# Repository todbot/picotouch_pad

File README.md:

# picotouch_pad
picotouch MIDI controller, but pad-based

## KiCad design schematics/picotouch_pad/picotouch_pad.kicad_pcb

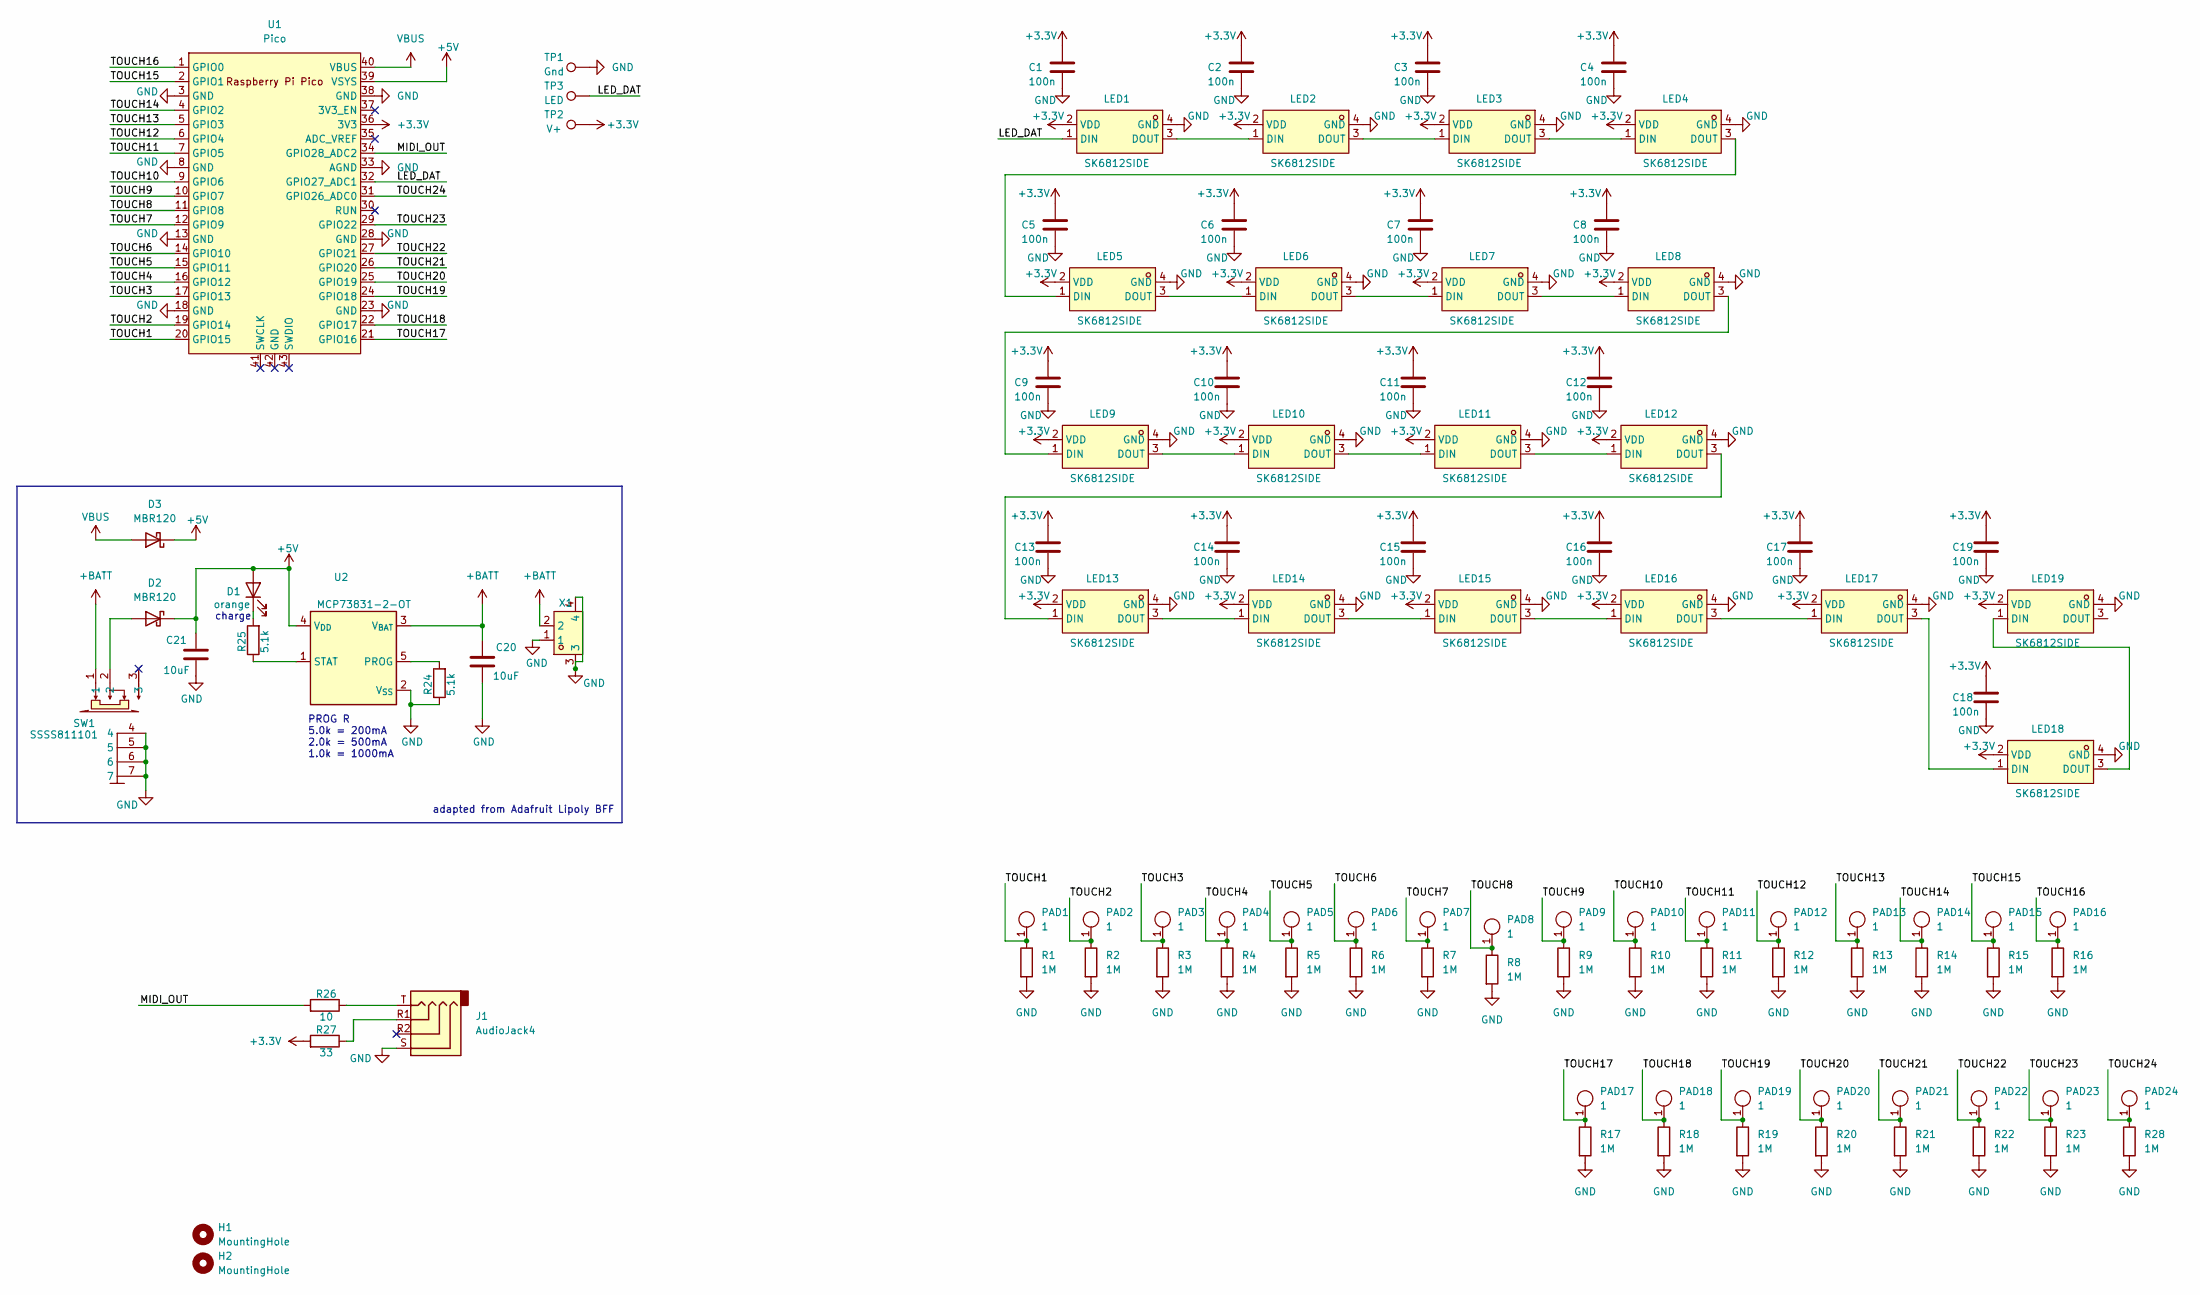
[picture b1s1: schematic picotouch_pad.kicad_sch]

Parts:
C1, C2, C3, C4, C5, C6, C7, C8, C9, C10, C11, C12, C13, C14, C15, C16, C17, C18, C19: 100n; C_0603_1608Metric
C20, C21: 10uF; C_0603_1608Metric
D1: orange; LED_0603_1608Metric
D2, D3: MBR120; D_SOD-123F; LCSC Part C130880
H1, H2: MountingHole; MountingHole_2.7mm_M2.5
J1: AudioJack4; Jack_3.5mm_PJ320D_Horizontal; LCSC C431535
LED1, LED2, LED3, LED4, LED5, LED6, LED7, LED8, LED9, LED10, LED11, LED12, LED13, LED14, LED15, LED16, LED17, LED18, LED19: SK6812SIDE; LED-SMD_4P-L4.0-W1.6-L-keepoutrev; LCSC Part C5378721
PAD1, PAD2, PAD3, PAD4, PAD5, PAD6, PAD7, PAD8, PAD9, PAD10, PAD11, PAD12, PAD13, PAD14, PAD15, PAD16: 1; Pad-CapTouch-10mm-roundrect
PAD17, PAD18, PAD19, PAD20, PAD21, PAD22, PAD23, PAD24: 1; Pad-CapTouch-10x5mm-roundrect
R1, R2, R3, R4, R5, R6, R7, R8, R9, R10, R11, R12, R13, R14, R15, R16, R17, R18, R19, R20, R21, R22, R23, R28: 1M; R_0603_1608Metric
R24, R25: 5.1k; R_0603_1608Metric
R26: 10; R_0603_1608Metric
R27: 33; R_0603_1608Metric
SW1: SSSS811101; SW-SMD_SSSS811101; LCSC Part C109335
TP1: Gnd; TestPoint_Pad_D1.5mm
TP2: V+; TestPoint_Pad_D1.5mm
TP3: LED; TestPoint_Pad_D1.5mm
U1: Pico; RPi_Pico_SMD
U2: MCP73831-2-OT; SOT-23-5; LCSC Part C424093
X1: AFC20-S02ACA-00; CONN-SMD_AFC20-S02ACA-00; LCSC Part C2764211

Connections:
+3.3V: C1.1, C2.1, C3.1, C4.1, C5.1, C6.1, C7.1, C8.1, C9.1, C10.1, C11.1, C12.1, C13.1, C14.1, C15.1, C16.1, C17.1, C18.1, C19.1, LED1.2 (VDD), LED2.2 (VDD), LED3.2 (VDD), LED4.2 (VDD), LED5.2 (VDD), LED6.2 (VDD), LED7.2 (VDD), LED8.2 (VDD), LED9.2 (VDD), LED10.2 (VDD), LED11.2 (VDD), LED12.2 (VDD), LED13.2 (VDD), LED14.2 (VDD), LED15.2 (VDD), LED16.2 (VDD), LED17.2 (VDD), LED18.2 (VDD), LED19.2 (VDD), R27.2, TP2.1, U1.36 (3V3)
+5V: C21.1, D1.2 (A), D2.1 (K), D3.1 (K), U1.39 (VSYS), U2.4 (V_{DD})
+BATT: C20.1, SW1.1, U2.3 (V_{BAT}), X1.2
/LED_DAT: LED1.1 (DIN), TP3.1, U1.32 (GPIO27_ADC1)
/MIDI_OUT: R26.2, U1.34 (GPIO28_ADC2)
/TOUCH1: PAD1.1 (A), R1.1, U1.20 (GPIO15)
/TOUCH2: PAD2.1 (A), R2.1, U1.19 (GPIO14)
/TOUCH3: PAD3.1 (A), R3.1, U1.17 (GPIO13)
/TOUCH4: PAD4.1 (A), R4.1, U1.16 (GPIO12)
/TOUCH5: PAD5.1 (A), R5.1, U1.15 (GPIO11)
/TOUCH6: PAD6.1 (A), R6.1, U1.14 (GPIO10)
/TOUCH7: PAD7.1 (A), R7.1, U1.12 (GPIO9)
/TOUCH8: PAD8.1 (A), R8.1, U1.11 (GPIO8)
/TOUCH9: PAD9.1 (A), R9.1, U1.10 (GPIO7)
/TOUCH10: PAD10.1 (A), R10.1, U1.9 (GPIO6)
/TOUCH11: PAD11.1 (A), R11.1, U1.7 (GPIO5)
/TOUCH12: PAD12.1 (A), R12.1, U1.6 (GPIO4)
/TOUCH13: PAD13.1 (A), R13.1, U1.5 (GPIO3)
/TOUCH14: PAD14.1 (A), R14.1, U1.4 (GPIO2)
/TOUCH15: PAD15.1 (A), R15.1, U1.2 (GPIO1)
/TOUCH16: PAD16.1 (A), R16.1, U1.1 (GPIO0)
/TOUCH17: PAD17.1 (A), R17.1, U1.21 (GPIO16)
/TOUCH18: PAD18.1 (A), R18.1, U1.22 (GPIO17)
/TOUCH19: PAD19.1 (A), R19.1, U1.24 (GPIO18)
/TOUCH20: PAD20.1 (A), R20.1, U1.25 (GPIO19)
/TOUCH21: PAD21.1 (A), R21.1, U1.26 (GPIO20)
/TOUCH22: PAD22.1 (A), R22.1, U1.27 (GPIO21)
/TOUCH23: PAD23.1 (A), R23.1, U1.29 (GPIO22)
/TOUCH24: PAD24.1 (A), R28.1, U1.31 (GPIO26_ADC0)
GND: C1.2, C2.2, C3.2, C4.2, C5.2, C6.2, C7.2, C8.2, C9.2, C10.2, C11.2, C12.2, C13.2, C14.2, C15.2, C16.2, C17.2, C18.2, C19.2, C20.2, C21.2, J1.S, LED1.4 (GND), LED2.4 (GND), LED3.4 (GND), LED4.4 (GND), LED5.4 (GND), LED6.4 (GND), LED7.4 (GND), LED8.4 (GND), LED9.4 (GND), LED10.4 (GND), LED11.4 (GND), LED12.4 (GND), LED13.4 (GND), LED14.4 (GND), LED15.4 (GND), LED16.4 (GND), LED17.4 (GND), LED18.4 (GND), LED19.4 (GND), R1.2, R2.2, R3.2, R4.2, R5.2, R6.2, R7.2, R8.2, R9.2, R10.2, R11.2, R12.2, R13.2, R14.2, R15.2, R16.2, R17.2, R18.2, R19.2, R20.2, R21.2, R22.2, R23.2, R24.1, R28.2, SW1.4, SW1.5, SW1.6, SW1.7, TP1.1, U1.3 (GND), U1.8 (GND), U1.13 (GND), U1.18 (GND), U1.23 (GND), U1.28 (GND), U1.33 (AGND), U1.38 (GND), U2.2 (V_{SS}), X1.1, X1.3, X1.4
unnamed: D1.1 (K), R25.2
unnamed: D2.2 (A), SW1.2
unnamed: J1.R1, R27.1
unnamed: J1.T, R26.1
unnamed: LED1.3 (DOUT), LED2.1 (DIN)
unnamed: LED2.3 (DOUT), LED3.1 (DIN)
unnamed: LED3.3 (DOUT), LED4.1 (DIN)
unnamed: LED4.3 (DOUT), LED5.1 (DIN)
unnamed: LED5.3 (DOUT), LED6.1 (DIN)
unnamed: LED6.3 (DOUT), LED7.1 (DIN)
unnamed: LED7.3 (DOUT), LED8.1 (DIN)
unnamed: LED8.3 (DOUT), LED9.1 (DIN)
unnamed: LED9.3 (DOUT), LED10.1 (DIN)
unnamed: LED10.3 (DOUT), LED11.1 (DIN)
unnamed: LED11.3 (DOUT), LED12.1 (DIN)
unnamed: LED12.3 (DOUT), LED13.1 (DIN)
unnamed: LED13.3 (DOUT), LED14.1 (DIN)
unnamed: LED14.3 (DOUT), LED15.1 (DIN)
unnamed: LED15.3 (DOUT), LED16.1 (DIN)
unnamed: LED16.3 (DOUT), LED17.1 (DIN)
unnamed: LED17.3 (DOUT), LED18.1 (DIN)
unnamed: LED18.3 (DOUT), LED19.1 (DIN)
unnamed: R24.2, U2.5 (PROG)
unnamed: R25.1, U2.1 (STAT)
VBUS: D3.2 (A), U1.40 (VBUS)

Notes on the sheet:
PROG R 5.0k = 200mA 2.0k = 500mA 1.0k = 1000mA
adapted from Adafruit Lipoly BFF
charge

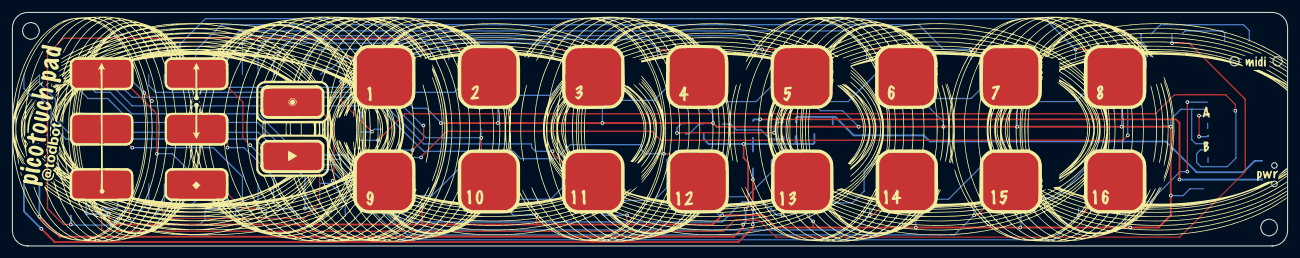
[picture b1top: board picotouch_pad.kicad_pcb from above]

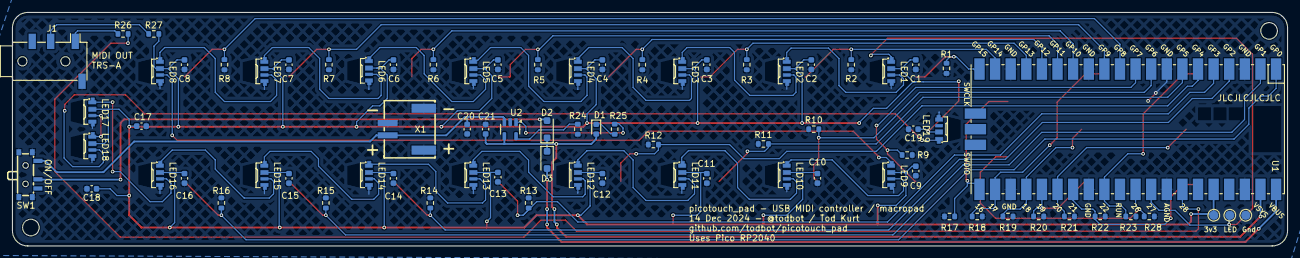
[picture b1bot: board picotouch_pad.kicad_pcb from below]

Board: 2 copper layers, 207.5 x 38.0 mm, 105 parts (79 on the bottom side), 55 nets.

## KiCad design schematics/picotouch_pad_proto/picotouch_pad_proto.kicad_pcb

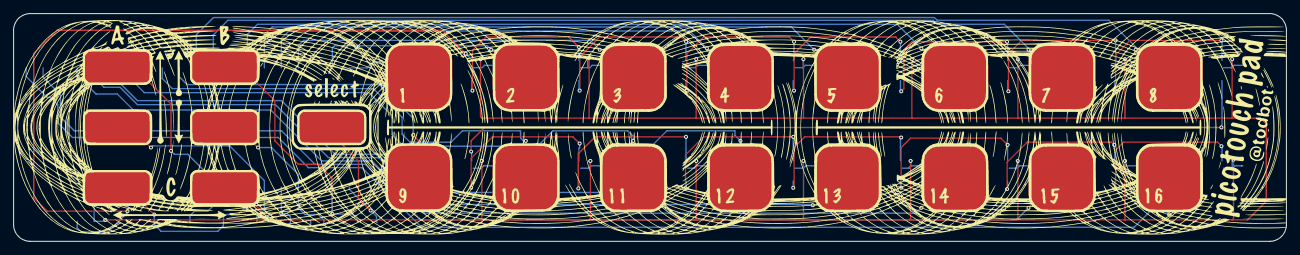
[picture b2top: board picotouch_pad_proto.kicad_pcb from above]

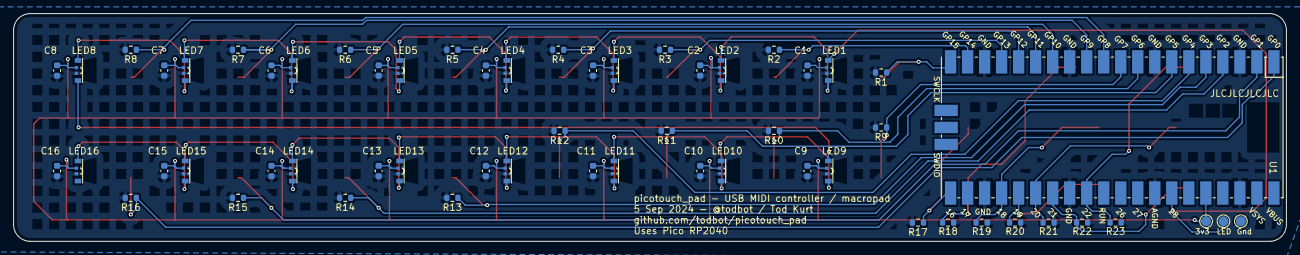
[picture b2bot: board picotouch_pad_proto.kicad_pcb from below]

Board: 2 copper layers, 190.0 x 34.0 mm, 82 parts (59 on the bottom side), 41 nets.

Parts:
C1, C2, C3, C4, C5, C6, C7, C8, C9, C10, C11, C12, C13, C14, C15, C16: 100n; C_0603_1608Metric
LED1, LED2, LED3, LED4, LED5, LED6, LED7, LED8, LED9, LED10, LED11, LED12, LED13, LED14, LED15, LED16: SK6805-EC3210R; LED-SMD_4P-L3.2-W1.5_SK6805-EC3210R-keepout
R1, R2, R3, R4, R5, R6, R7, R8, R9, R10, R11, R12, R13, R14, R15, R16, R17, R18, R19, R20, R21, R22, R23: 1M; R_0603_1608Metric
SW1, SW2, SW3, SW4, SW5, SW6, SW7, SW8, SW9, SW10, SW11, SW12, SW13, SW14, SW15, SW16: 1; Pad-CapTouch-10mm-roundrect
SW17, SW18, SW19, SW20, SW21, SW22, SW23: 1; Pad-CapTouch-10x5mm-roundrect
TP1: Gnd; TestPoint_Pad_D1.5mm
TP2: V+; TestPoint_Pad_D1.5mm
TP3: LED; TestPoint_Pad_D1.5mm
U1: Pico; RPi_Pico_SMD

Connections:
+3.3V: C1.1, C2.1, C3.1, C4.1, C5.1, C6.1, C7.1, C8.1, C9.1, C10.1, C11.1, C12.1, C13.1, C14.1, C15.1, C16.1, LED1.4 (VDD), LED2.4 (VDD), LED3.4 (VDD), LED4.4 (VDD), LED5.4 (VDD), LED6.4 (VDD), LED7.4 (VDD), LED8.4 (VDD), LED9.4 (VDD), LED10.4 (VDD), LED11.4 (VDD), LED12.4 (VDD), LED13.4 (VDD), LED14.4 (VDD), LED15.4 (VDD), LED16.4 (VDD), TP2.1, U1.36 (3V3)
/LED_DAT: LED1.3 (DIN), TP3.1, U1.34 (GPIO28_ADC2)
/TOUCH1: R1.1, SW1.1 (A), U1.20 (GPIO15)
/TOUCH2: R2.1, SW2.1 (A), U1.19 (GPIO14)
/TOUCH3: R3.1, SW3.1 (A), U1.17 (GPIO13)
/TOUCH4: R4.1, SW4.1 (A), U1.16 (GPIO12)
/TOUCH5: R5.1, SW5.1 (A), U1.15 (GPIO11)
/TOUCH6: R6.1, SW6.1 (A), U1.14 (GPIO10)
/TOUCH7: R7.1, SW7.1 (A), U1.12 (GPIO9)
/TOUCH8: R8.1, SW8.1 (A), U1.11 (GPIO8)
/TOUCH9: R9.1, SW9.1 (A), U1.10 (GPIO7)
/TOUCH10: R10.1, SW10.1 (A), U1.9 (GPIO6)
/TOUCH11: R11.1, SW11.1 (A), U1.7 (GPIO5)
/TOUCH12: R12.1, SW12.1 (A), U1.6 (GPIO4)
/TOUCH13: R13.1, SW13.1 (A), U1.5 (GPIO3)
/TOUCH14: R14.1, SW14.1 (A), U1.4 (GPIO2)
/TOUCH15: R15.1, SW15.1 (A), U1.2 (GPIO1)
/TOUCH16: R16.1, SW16.1 (A), U1.1 (GPIO0)
/TOUCH17: R17.1, SW17.1 (A), U1.21 (GPIO16)
/TOUCH18: R18.1, SW18.1 (A), U1.22 (GPIO17)
/TOUCH19: R19.1, SW19.1 (A), U1.24 (GPIO18)
/TOUCH20: R20.1, SW20.1 (A), U1.25 (GPIO19)
/TOUCH21: R21.1, SW21.1 (A), U1.26 (GPIO20)
/TOUCH22: R22.1, SW22.1 (A), U1.27 (GPIO21)
/TOUCH23: R23.1, SW23.1 (A), U1.29 (GPIO22)
GND: C1.2, C2.2, C3.2, C4.2, C5.2, C6.2, C7.2, C8.2, C9.2, C10.2, C11.2, C12.2, C13.2, C14.2, C15.2, C16.2, LED1.1 (GND), LED2.1 (GND), LED3.1 (GND), LED4.1 (GND), LED5.1 (GND), LED6.1 (GND), LED7.1 (GND), LED8.1 (GND), LED9.1 (GND), LED10.1 (GND), LED11.1 (GND), LED12.1 (GND), LED13.1 (GND), LED14.1 (GND), LED15.1 (GND), LED16.1 (GND), R1.2, R2.2, R3.2, R4.2, R5.2, R6.2, R7.2, R8.2, R9.2, R10.2, R11.2, R12.2, R13.2, R14.2, R15.2, R16.2, R17.2, R18.2, R19.2, R20.2, R21.2, R22.2, R23.2, TP1.1, U1.3 (GND), U1.8 (GND), U1.13 (GND), U1.18 (GND), U1.23 (GND), U1.28 (GND), U1.33 (AGND), U1.38 (GND)
unnamed: LED1.2 (DOUT), LED2.3 (DIN)
unnamed: LED2.2 (DOUT), LED3.3 (DIN)
unnamed: LED3.2 (DOUT), LED4.3 (DIN)
unnamed: LED4.2 (DOUT), LED5.3 (DIN)
unnamed: LED5.2 (DOUT), LED6.3 (DIN)
unnamed: LED6.2 (DOUT), LED7.3 (DIN)
unnamed: LED7.2 (DOUT), LED8.3 (DIN)
unnamed: LED8.2 (DOUT), LED9.3 (DIN)
unnamed: LED9.2 (DOUT), LED10.3 (DIN)
unnamed: LED10.2 (DOUT), LED11.3 (DIN)
unnamed: LED11.2 (DOUT), LED12.3 (DIN)
unnamed: LED12.2 (DOUT), LED13.3 (DIN)
unnamed: LED13.2 (DOUT), LED14.3 (DIN)
unnamed: LED14.2 (DOUT), LED15.3 (DIN)
unnamed: LED15.2 (DOUT), LED16.3 (DIN)

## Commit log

2024-09-06 first
2024-09-06 files as sent to fab
2024-09-12 new pcb with sk6812side
2024-09-16 add battery circuit
2024-09-16 add midi out
2024-09-16 cleanup
2024-09-20 new silkscreen and fixes
2024-09-20 picotouch_pad_proto test code
2024-09-20 add picotouch_pad_proto pcb
2024-09-21 picopad_touch_proto code update
2024-09-21 octave & mod wheel buttons work on picotouch_pad_proto
2024-09-23 resize, cleanup, change battery charge chip sch symbol
2024-09-25 picotouch_pad_proto code: add midi receive
2024-09-30 picotouch_pad_proto: add modwheel ramping
2024-10-10 add vbus diode, fix up power layout a bit
2024-11-16 cleanup and new silkscreen
2024-11-16 more layout tuning
2024-12-15 demo code as in video 14 Dec 2024
2024-12-15 one net forgot! fix +5V to VSYS
